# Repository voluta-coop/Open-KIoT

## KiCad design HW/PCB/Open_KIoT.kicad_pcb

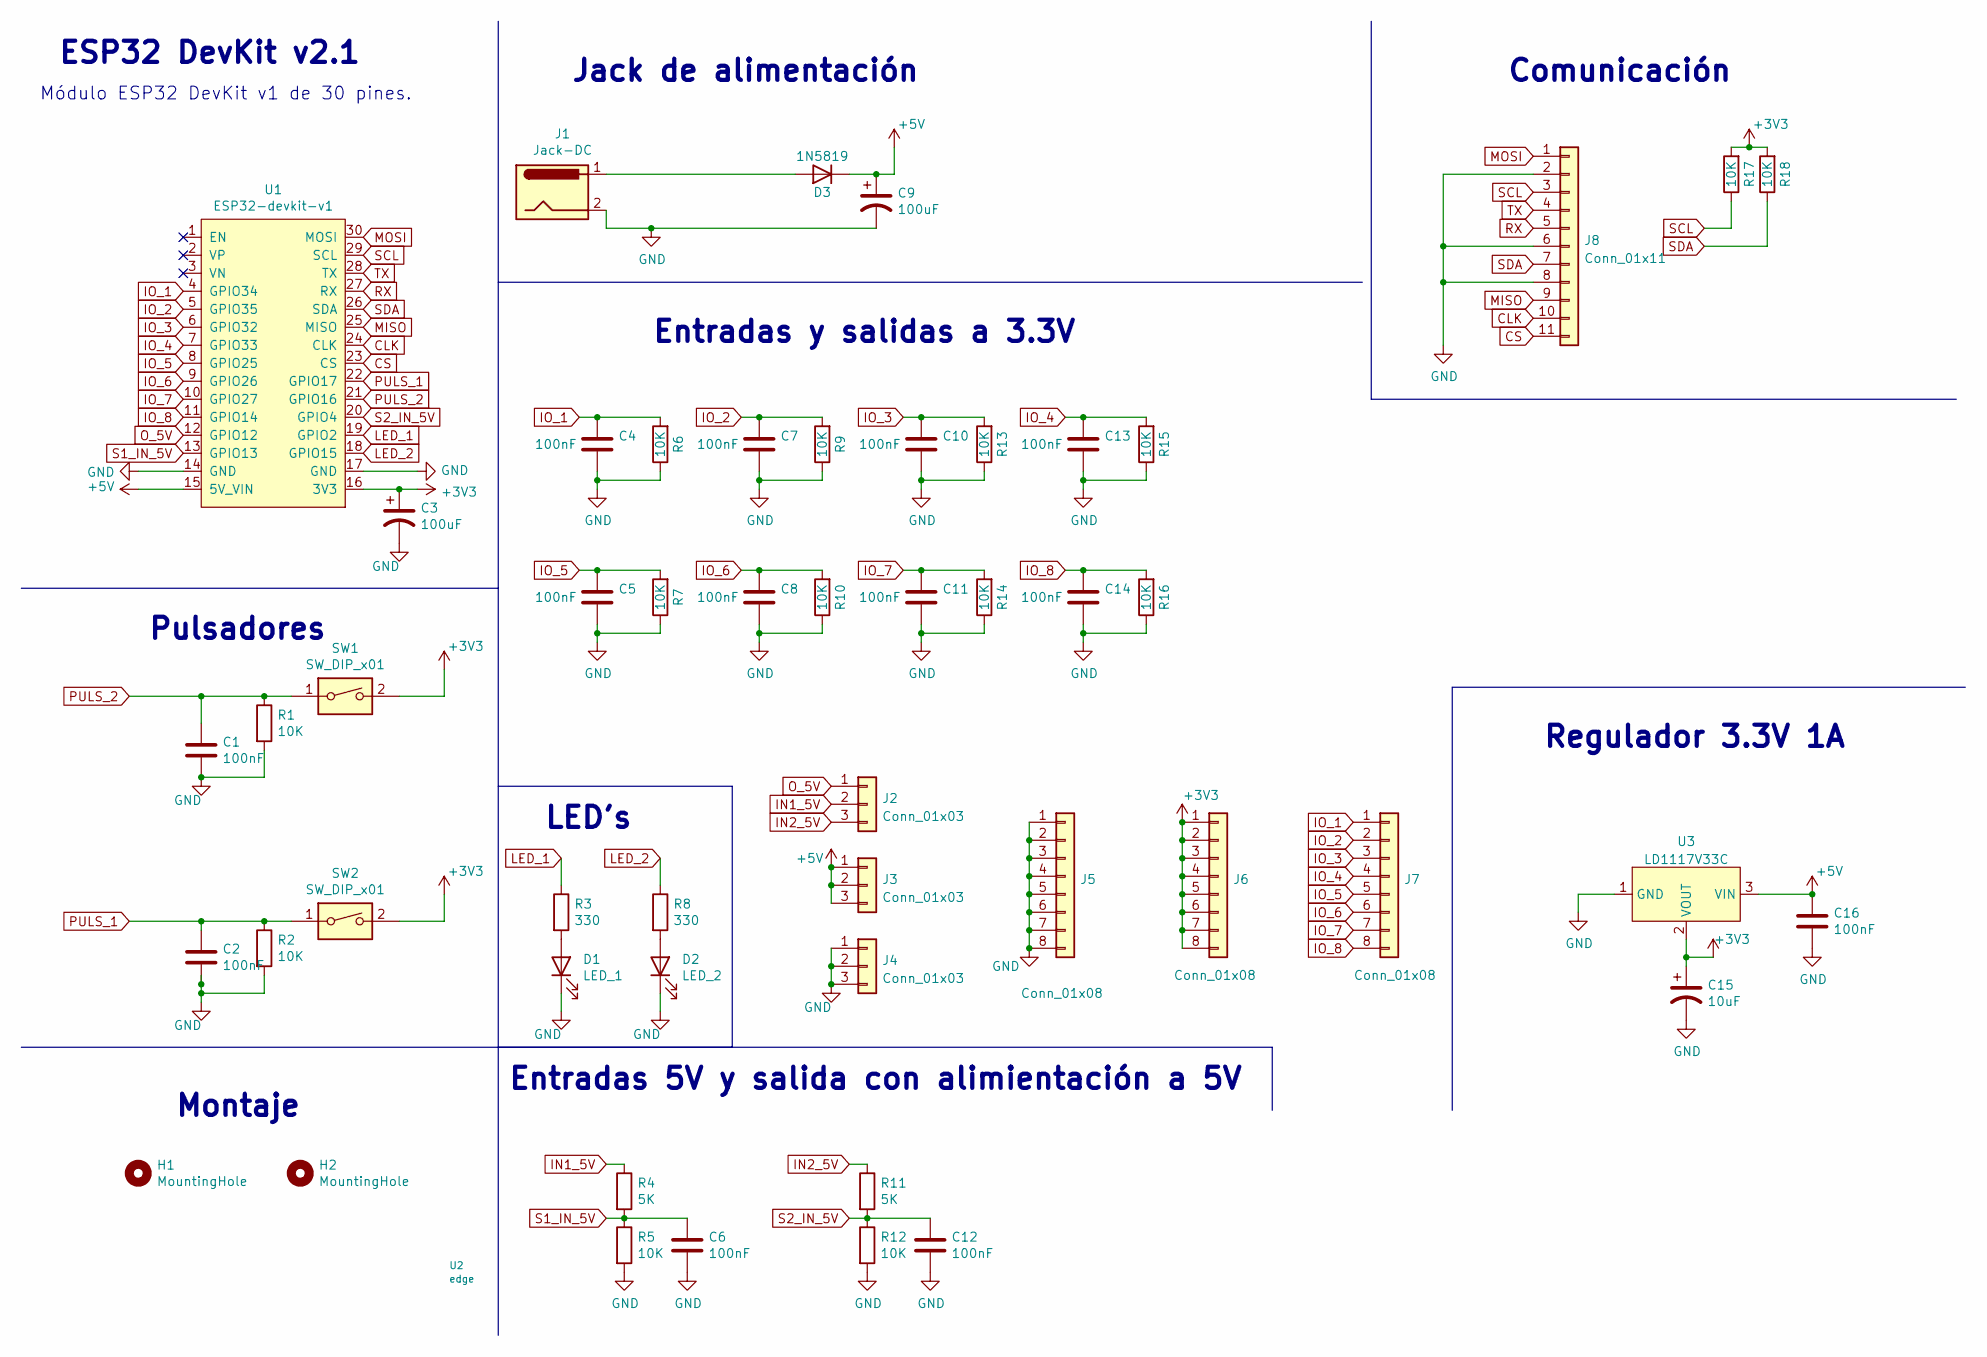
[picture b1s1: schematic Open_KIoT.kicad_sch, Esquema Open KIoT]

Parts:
C1, C2, C4, C5, C6, C7, C8, C10, C11, C12, C13, C14, C16: 100nF; C_Disc_D3.8mm_W2.6mm_P2.50mm
C3, C9: 100uF; CP_Radial_D5.0mm_P2.00mm
C15: 10uF; CP_Radial_D5.0mm_P2.00mm
D1: LED_1; LED_D5.0mm_Clear
D2: LED_2; LED_D5.0mm_Clear
D3: 1N5819; D_DO-41_SOD81_P12.70mm_Horizontal
H1, H2: MountingHole; MountingHole_3.2mm_M3_Pad_Via
J1: Jack-DC; BarrelJack_Horizontal
J2, J3, J4: Conn_01x03; PinHeader_1x03_P2.54mm_Vertical
J5, J6, J7: Conn_01x08; PinHeader_1x08_P2.54mm_Vertical
J8: Conn_01x11; PinHeader_1x11_P2.54mm_Vertical
R1, R2, R5, R6, R7, R9, R10, R12, R13, R14, R15, R16, R17, R18: 10K; R_Axial_DIN0207_L6.3mm_D2.5mm_P7.62mm_Horizontal
R3, R8: 330; R_Axial_DIN0207_L6.3mm_D2.5mm_P7.62mm_Horizontal
R4, R11: 5K; R_Axial_DIN0207_L6.3mm_D2.5mm_P7.62mm_Horizontal
SW1, SW2: SW_DIP_x01; SW_PUSH_6mm_H4.3mm
U1: ESP32-devkit-v1; ESP32-DevKit-v1
U2: edge; edge_2
U3: LD1117V33C; TO-220F-3_Vertical

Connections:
+3V3: C3.1, C15.1, J6.1, J6.2, J6.3, J6.4, J6.5, J6.6, J6.7, J6.8, R17.2, R18.2, SW1.2, SW2.2, U1.16 (3V3), U3.2 (VOUT)
+5V: C9.1, C16.1, D3.1 (K), J3.1, J3.2, J3.3, U1.15 (5V_VIN), U3.3 (VIN)
CLK: J8.10, U1.24 (CLK)
CS: J8.11, U1.23 (CS)
GND: C1.2, C2.2, C3.2, C4.2, C5.2, C6.2, C7.2, C8.2, C9.2, C10.2, C11.2, C12.2, C13.2, C14.2, C15.2, C16.2, D1.1 (K), D2.1 (K), J1.2, J4.1, J4.2, J4.3, J5.1, J5.2, J5.3, J5.4, J5.5, J5.6, J5.7, J5.8, J8.2, J8.6, J8.8, R1.2, R2.2, R5.2, R6.1, R7.1, R9.1, R10.1, R12.2, R13.1, R14.1, R15.1, R16.1, U1.14 (GND), U1.17 (GND), U3.1 (GND)
IN1_5V: J2.2, R4.1
IN2_5V: J2.3, R11.1
IO_1: C4.1, J7.1, R6.2, U1.4 (GPIO34)
IO_2: C7.1, J7.2, R9.2, U1.5 (GPIO35)
IO_3: C10.1, J7.3, R13.2, U1.6 (GPIO32)
IO_4: C13.1, J7.4, R15.2, U1.7 (GPIO33)
IO_5: C5.1, J7.5, R7.2, U1.8 (GPIO25)
IO_6: C8.1, J7.6, R10.2, U1.9 (GPIO26)
IO_7: C11.1, J7.7, R14.2, U1.10 (GPIO27)
IO_8: C14.1, J7.8, R16.2, U1.11 (GPIO14)
LED_1: R3.1, U1.19 (GPIO2)
LED_2: R8.1, U1.18 (GPIO15)
MISO: J8.9, U1.25 (MISO)
MOSI: J8.1, U1.30 (MOSI)
unnamed: D1.2 (A), R3.2
unnamed: D2.2 (A), R8.2
unnamed: D3.2 (A), J1.1
O_5V: J2.1, U1.12 (GPIO12)
PULS_1: C2.1, R2.1, SW2.1, U1.22 (GPIO17)
PULS_2: C1.1, R1.1, SW1.1, U1.21 (GPIO16)
RX: J8.5, U1.27 (RX)
S1_IN_5V: C6.1, R4.2, R5.1, U1.13 (GPIO13)
S2_IN_5V: C12.1, R11.2, R12.1, U1.20 (GPIO4)
SCL: J8.3, R17.1, U1.29 (SCL)
SDA: J8.7, R18.1, U1.26 (SDA)
TX: J8.4, U1.28 (TX)

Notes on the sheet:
Regulador 3.3V 1A
Módulo ESP32 DevKit v1 de 30 pines.
Entradas 5V y salida con alimientación a 5V
Pulsadores
Entradas y salidas a 3.3V
Comunicación
Montaje
ESP32 DevKit v2.1
LED's
Jack de alimentación

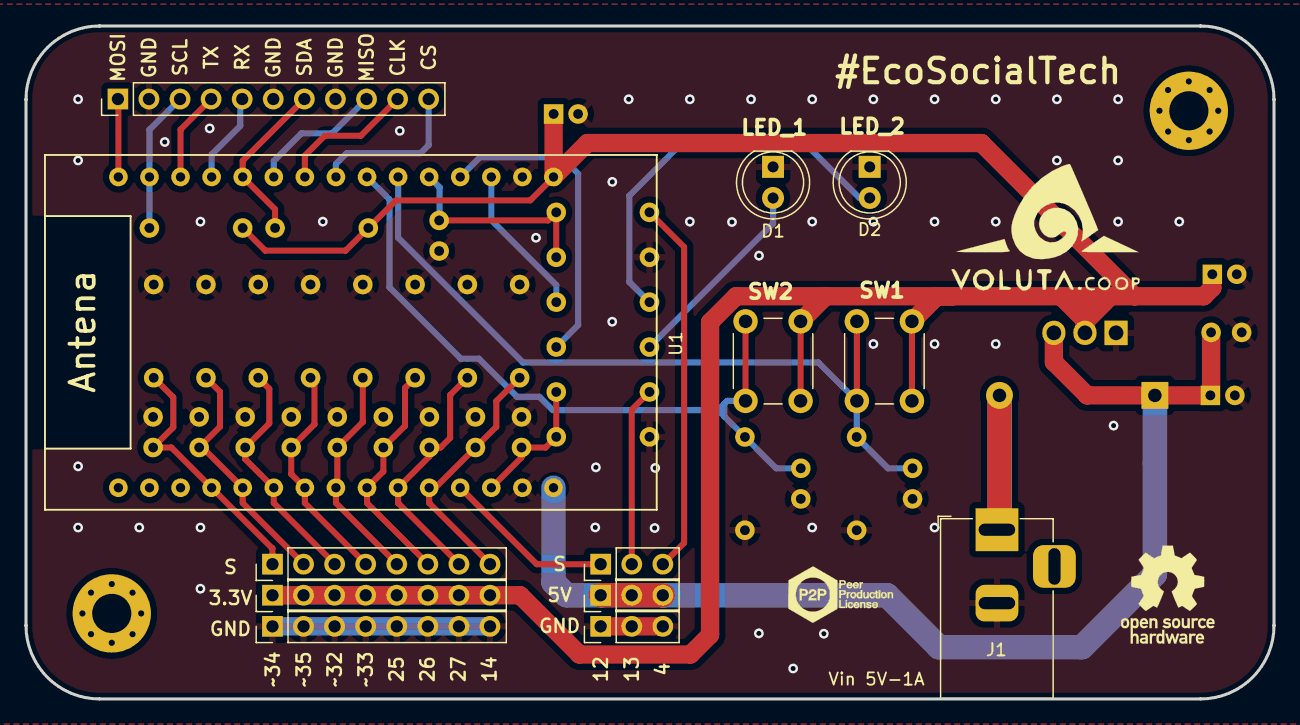
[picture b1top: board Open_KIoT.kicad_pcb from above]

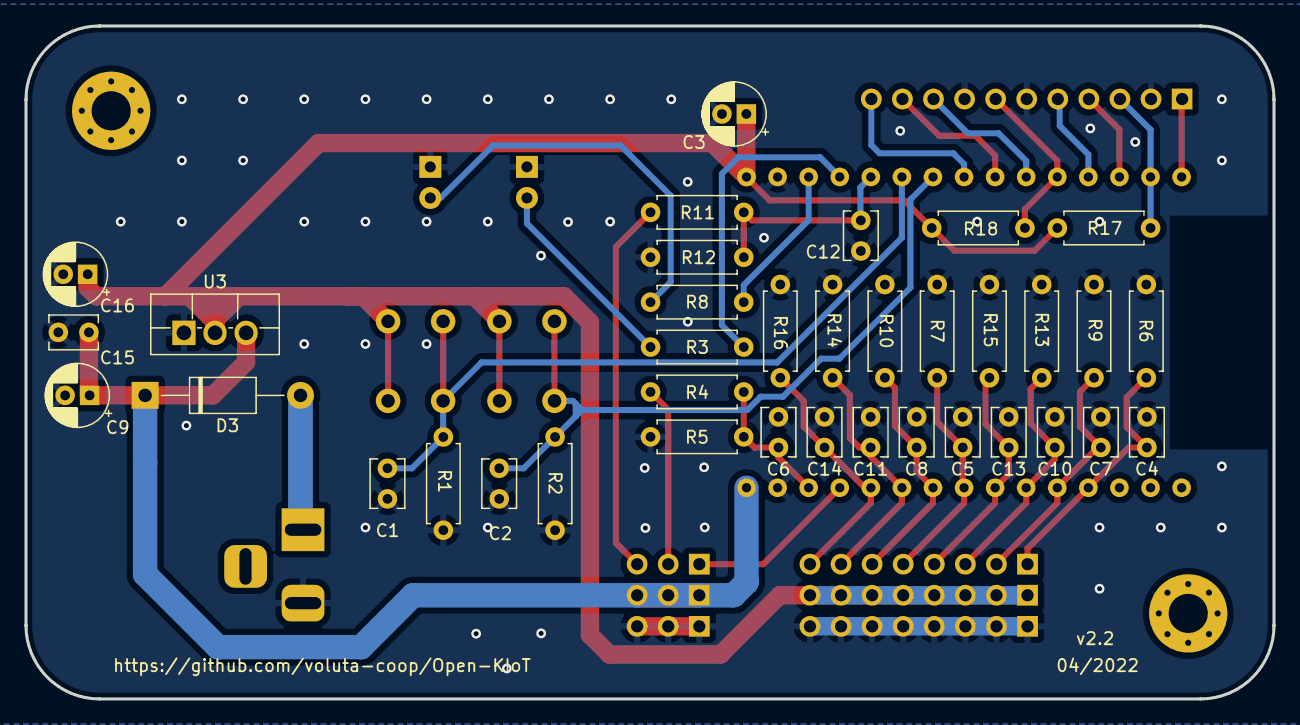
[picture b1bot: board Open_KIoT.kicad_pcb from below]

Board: 2 copper layers, 102.0 x 55.0 mm, 51 parts (36 on the bottom side), 31 nets.

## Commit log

2022-04-28 Inicio el repositorio de Open KIoT
2022-04-29 Añadido el test del sensor DHT11 con bot de Telegram
2022-04-29 Reestructuración de carpetas
2022-04-29 Archivo oculto eliminado
2022-05-02 Icluido el esquema de la PCB en PDF
2022-05-02 Reestructuracion carpetas y esquema PCB en PDF añadido
2022-05-02 Corrección errores valores resistencias
2022-05-02 Reestructuración carpetas
2022-05-03 Corrección error merge
2022-05-03 Corrección error esquema
2022-05-03 .gitignore añadido
2022-05-06 Añadido doc con instrucciones de soldadura e imágenes de la PCB
2022-05-06 gitignore actualizado
2022-05-06 Corrección errata doc instrucciones
2022-05-06 Añadido contacto en documento instrucciones
2022-05-19 Piezas añadidas: caja PCB Open KIoT, carcasa final de carrera, soporte sensor IR, caja ESP32-CAM
2022-05-23 Archivos 3D añadidos
2022-05-23 FW de test añadido
2022-05-23 FW erroneo eliminado
2022-05-23 Corrección código TEST
2022-05-24 Código de demostración
2022-06-02 Piezas 3D actualizadas
2022-06-20 Mejora carcasa ESP32-CAM
2022-06-27 Actualización FW ESP32-cam
2022-06-27 Corrección FW Test_Riego
2022-07-08 Simplificación de TEST_Riego.ino
2022-07-11 Primera versión del código añadida
2022-07-11 Limpieza de archivos
2022-07-12 Avances en código
2022-07-12 Corrección archivos
2022-07-21 FW actualizado y piezas 3D añadidas
2022-07-25 FW actualizado
2022-07-30 Firmware eGallinero funcional + piezas 3D actualizadas
2022-08-02 Corrección FW
